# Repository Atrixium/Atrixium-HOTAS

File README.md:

# Atrixium-HOTAS

This is a simple HOTAS flight stick for Sparkfun Pro Micro boards (and clones) it uses the excellent NicoHood Gamepad API as the core https://github.com/NicoHood/HID as well as leveraging the SPI library for efficiently reading the shift registers. The code is pretty rough but is functional and it's fast enough for real gameplay, I have plans to integrate a better ADC in the future in the form of the Adafruit ADS1115 16bit, 4 channel ADC.

Schematics and board files are in CADsoft Eagle format.

Additional info on this HOTAS can be found on my Youtube channel: https://www.youtube.com/user/Atrixium

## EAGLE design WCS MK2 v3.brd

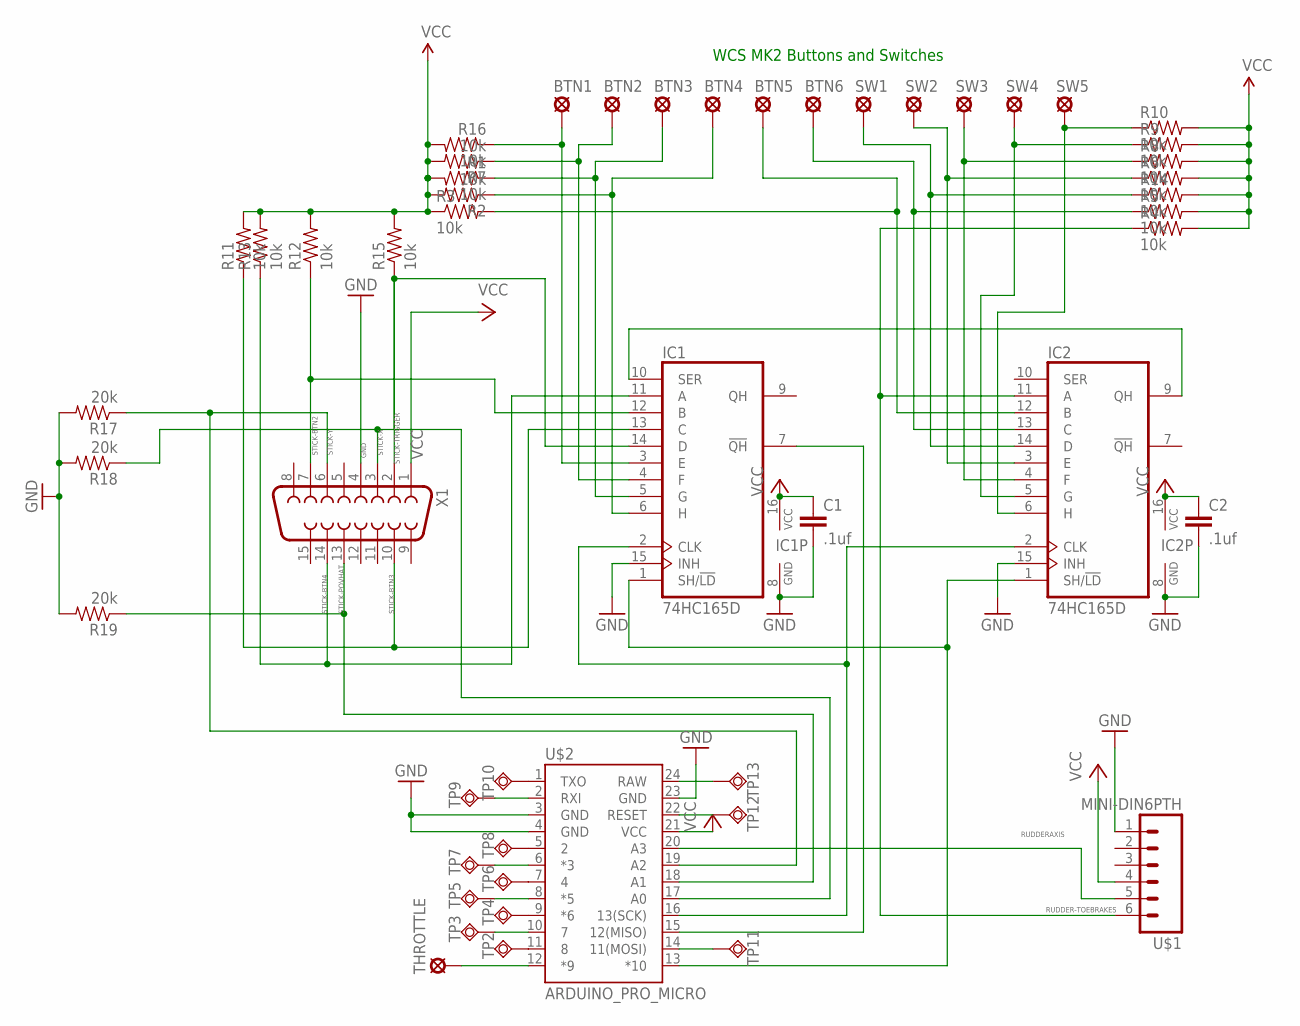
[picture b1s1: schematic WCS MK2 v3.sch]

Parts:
BTN1, BTN2, BTN3, BTN4, BTN5, BTN6: LSP10
C1, C2: .1uf; C025-060X050
IC1, IC2: 74HC165D; SO16
R1, R2, R3, R4, R5, R6, R7, R8, R9, R10, R11, R12, R13, R14, R15, R16: 10k; AXIAL-0.1
R17, R18, R19: 20k; AXIAL-0.1
SW1, SW2, SW3, SW4, SW5: LSP10
THROTTLE: LSP10
TP2, TP3, TP4, TP5, TP6, TP7, TP8, TP9, TP10, TP11, TP12, TP13: TPSQTP20SQ; TP20SQ
U$1: MINI-DIN6PTH; MINI-DIN6
U$2: ARDUINO_PRO_MICRO
X1: F15HP

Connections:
CLOCK: IC1.2 (CLK), IC2.2 (CLK), U$2.16 (13(SCK))
DAISYCHAIN: IC1.10 (SER), IC2.9 (QH)
GND: C1.2, C2.2, IC1.8 (GND), IC1.15 (INH), IC2.8 (GND), IC2.15 (INH), R17.P$2 (2), R18.P$2 (2), R19.P$2 (2), U$1.1, U$2.3 (GND), U$2.4 (GND), U$2.23 (GND), X1.4
MISO: IC1.7 (!QH), U$2.15 (12(MISO))
unnamed: BTN1.MP, IC1.3 (E), R16.P$1 (1)
unnamed: BTN2.MP, IC1.4 (F), R7.P$1 (1)
unnamed: BTN3.MP, IC1.5 (G), R1.P$1 (1)
unnamed: BTN4.MP, IC1.6 (H), R2.P$1 (1)
unnamed: IC2.6 (H), R10.P$1 (1), SW5.MP
unnamed: IC2.5 (G), R9.P$1 (1), SW4.MP
unnamed: IC2.4 (F), R8.P$1 (1), SW3.MP
unnamed: IC2.3 (E), R6.P$1 (1), SW2.MP
unnamed: IC2.14 (D), R14.P$1 (1), SW1.MP
unnamed: BTN6.MP, IC2.13 (C), R5.P$1 (1)
unnamed: BTN5.MP, IC2.12 (B), R3.P$2 (2)
unnamed: TP2.TP, U$2.11 (8)
unnamed: TP3.TP, U$2.10 (7)
unnamed: TP4.TP, U$2.9 (*6)
unnamed: TP5.TP, U$2.8 (*5)
unnamed: TP6.TP, U$2.7 (4)
unnamed: TP7.TP, U$2.6 (*3)
unnamed: TP8.TP, U$2.5 (2)
unnamed: TP9.TP, U$2.2 (RXI)
unnamed: TP10.TP, U$2.1 (TXO)
unnamed: TP11.TP, U$2.14 (11(MOSI))
unnamed: TP12.TP, U$2.22 (RESET)
unnamed: TP13.TP, U$2.24 (RAW)
RUDDER-TOEBRAKES: IC2.11 (A), R4.P$1 (1), U$1.6
RUDDERAXIS: U$1.5, U$2.20 (A3)
SR-LOAD: IC1.1 (SH/!LD), IC2.1 (SH/!LD), U$2.13 (*10)
STICK-BTN2: IC1.12 (B), R12.P$1 (1), X1.7
STICK-BTN3: IC1.13 (C), R11.P$1 (1), X1.10
STICK-BTN4: IC1.11 (A), R13.P$1 (1), X1.14
STICK-POVHAT: R19.P$1 (1), U$2.18 (A1), X1.13
STICK-TRIGGER: IC1.14 (D), R15.P$1 (1), X1.2
STICK-X: R18.P$1 (1), U$2.17 (A0), X1.3
STICK-Y: R17.P$1 (1), U$2.19 (A2), X1.6
THROTTLEAXIS: THROTTLE.MP, U$2.12 (*9)
VCC: C1.1, C2.1, IC1.16 (VCC), IC2.16 (VCC), R1.P$2 (2), R2.P$2 (2), R3.P$1 (1), R4.P$2 (2), R5.P$2 (2), R6.P$2 (2), R7.P$2 (2), R8.P$2 (2), R9.P$2 (2), R10.P$2 (2), R11.P$2 (2), R12.P$2 (2), R13.P$2 (2), R14.P$2 (2), R15.P$2 (2), R16.P$2 (2), U$1.4, U$2.21 (VCC), X1.1

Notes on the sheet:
WCS MK2 Buttons and Switches

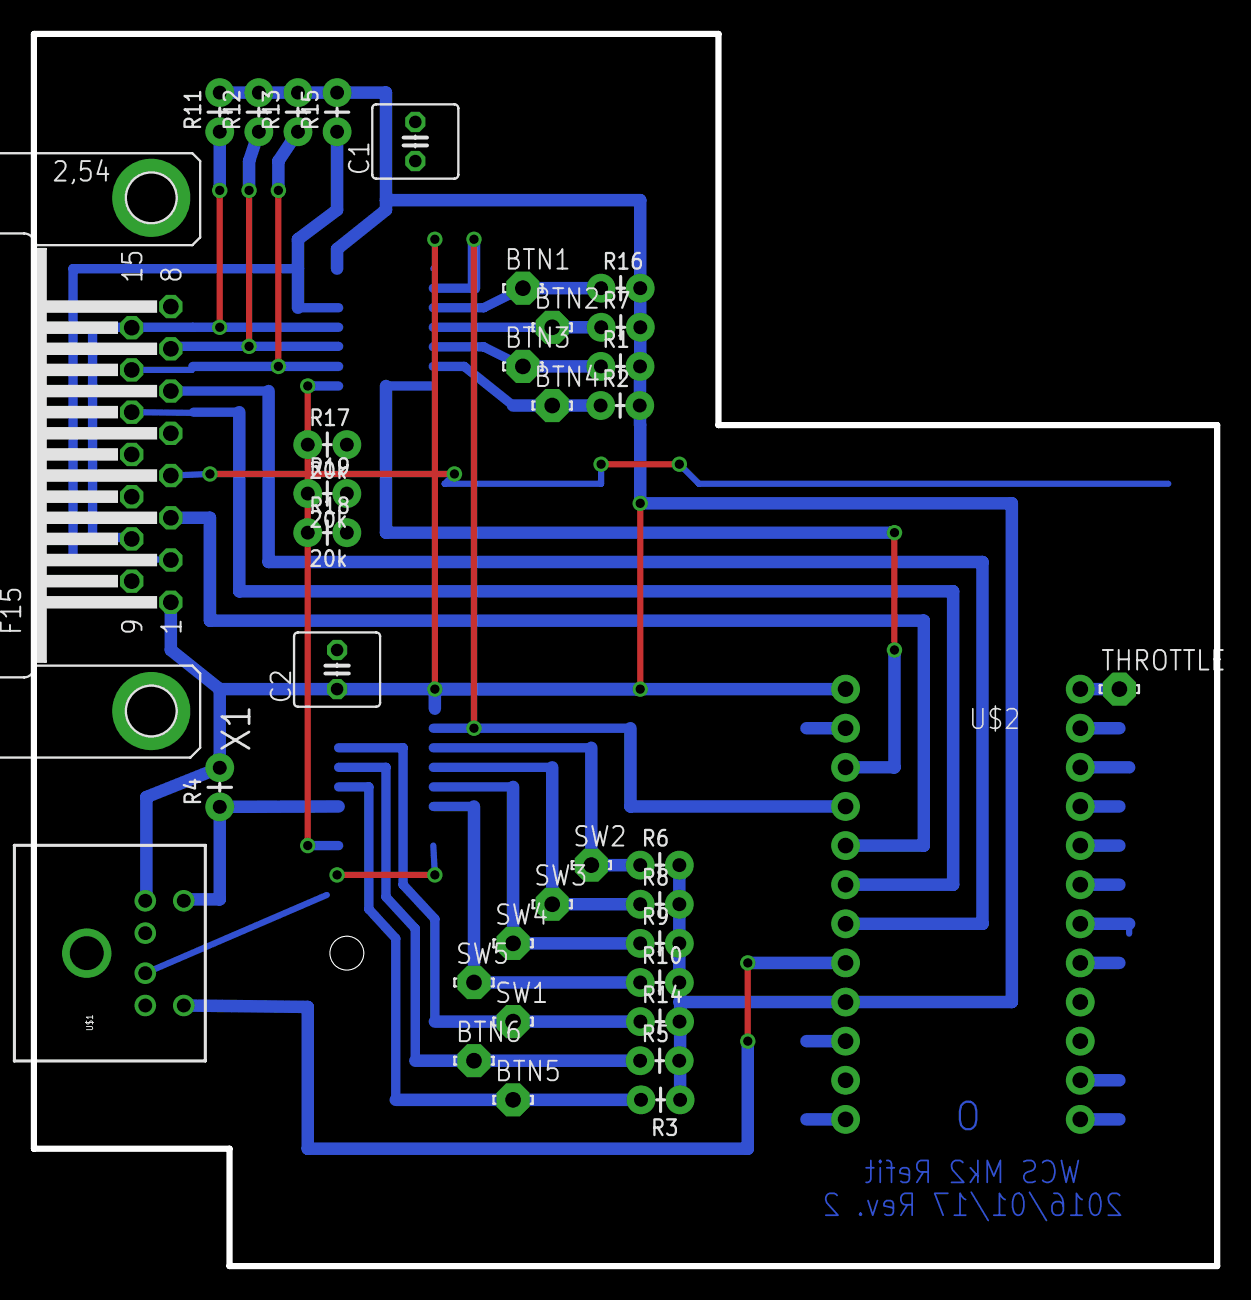
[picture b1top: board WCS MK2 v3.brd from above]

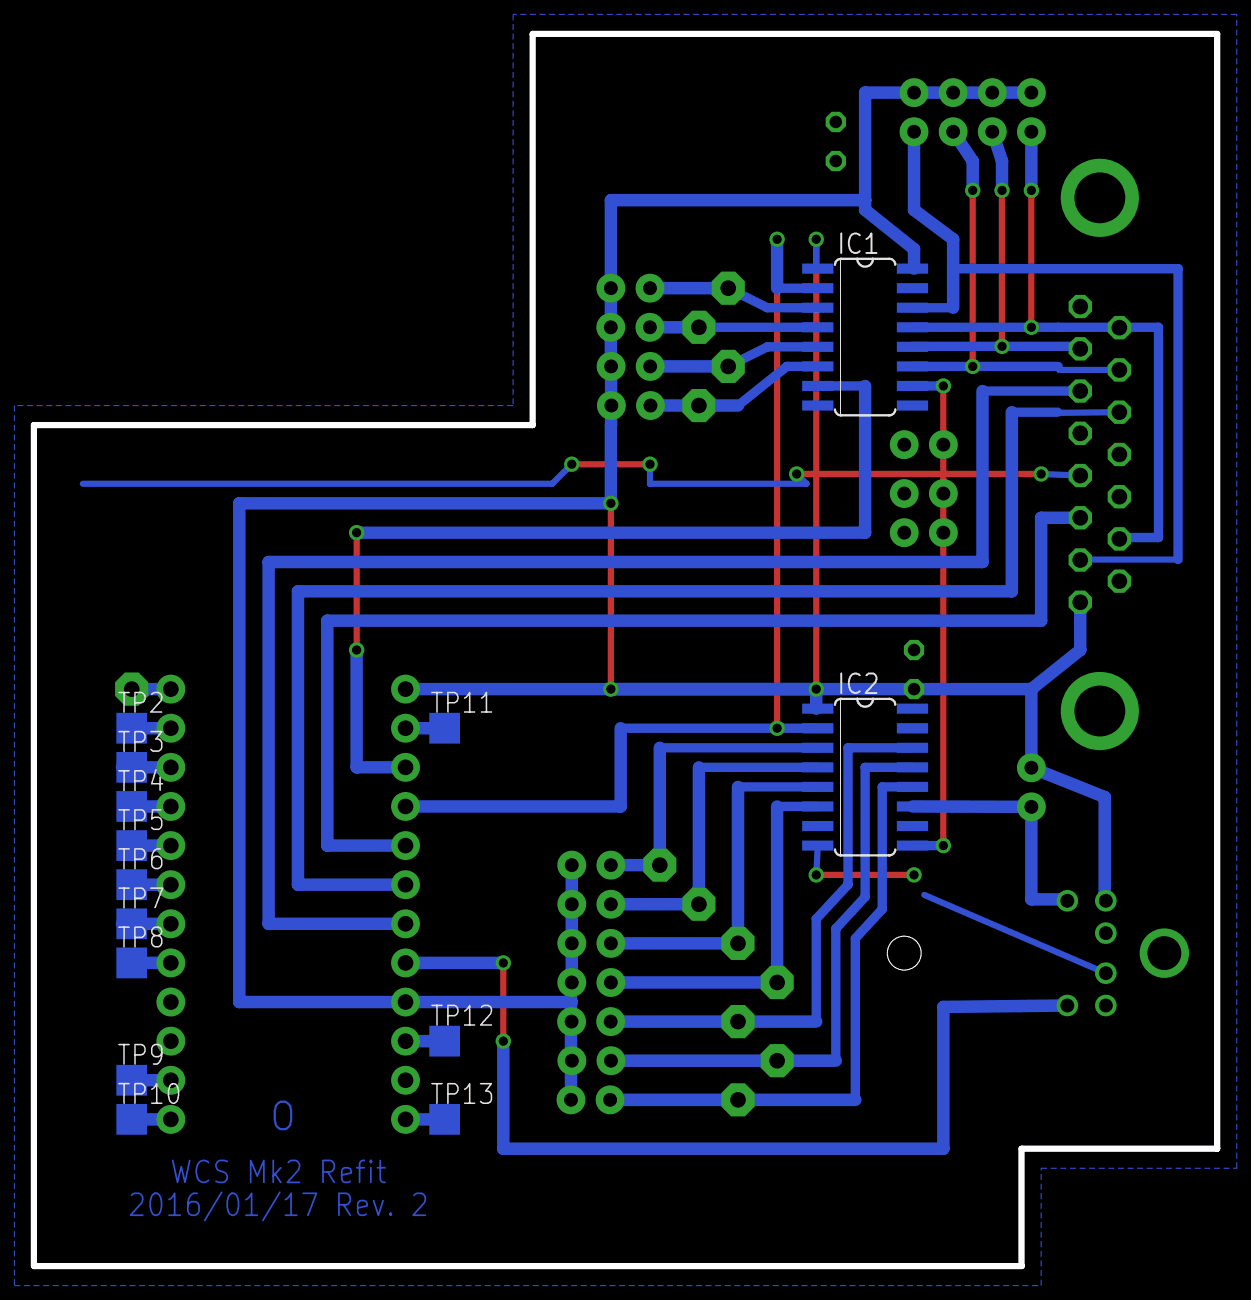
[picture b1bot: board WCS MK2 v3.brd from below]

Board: 2 copper layers, 76.8 x 80.0 mm, 50 parts (14 on the bottom side), 39 nets.

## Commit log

2018-02-16 Intial commit
2018-02-16 Rename Gamepad-Rob.ino to Atrixium-hotas.ino
2020-03-18 Add files via upload
    Added schematic, board layout, SO16 breakout board, Top Gun pinouts and original design document.
2020-03-18 Add files via upload
    Add button, throttle and rudder wiring info

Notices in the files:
parts and their libraries:
SparkFun-Connectors: Licensing: Creative Commons ShareAlike 4.0 International - https://creativecommons.org/licenses/by-sa/4.0
